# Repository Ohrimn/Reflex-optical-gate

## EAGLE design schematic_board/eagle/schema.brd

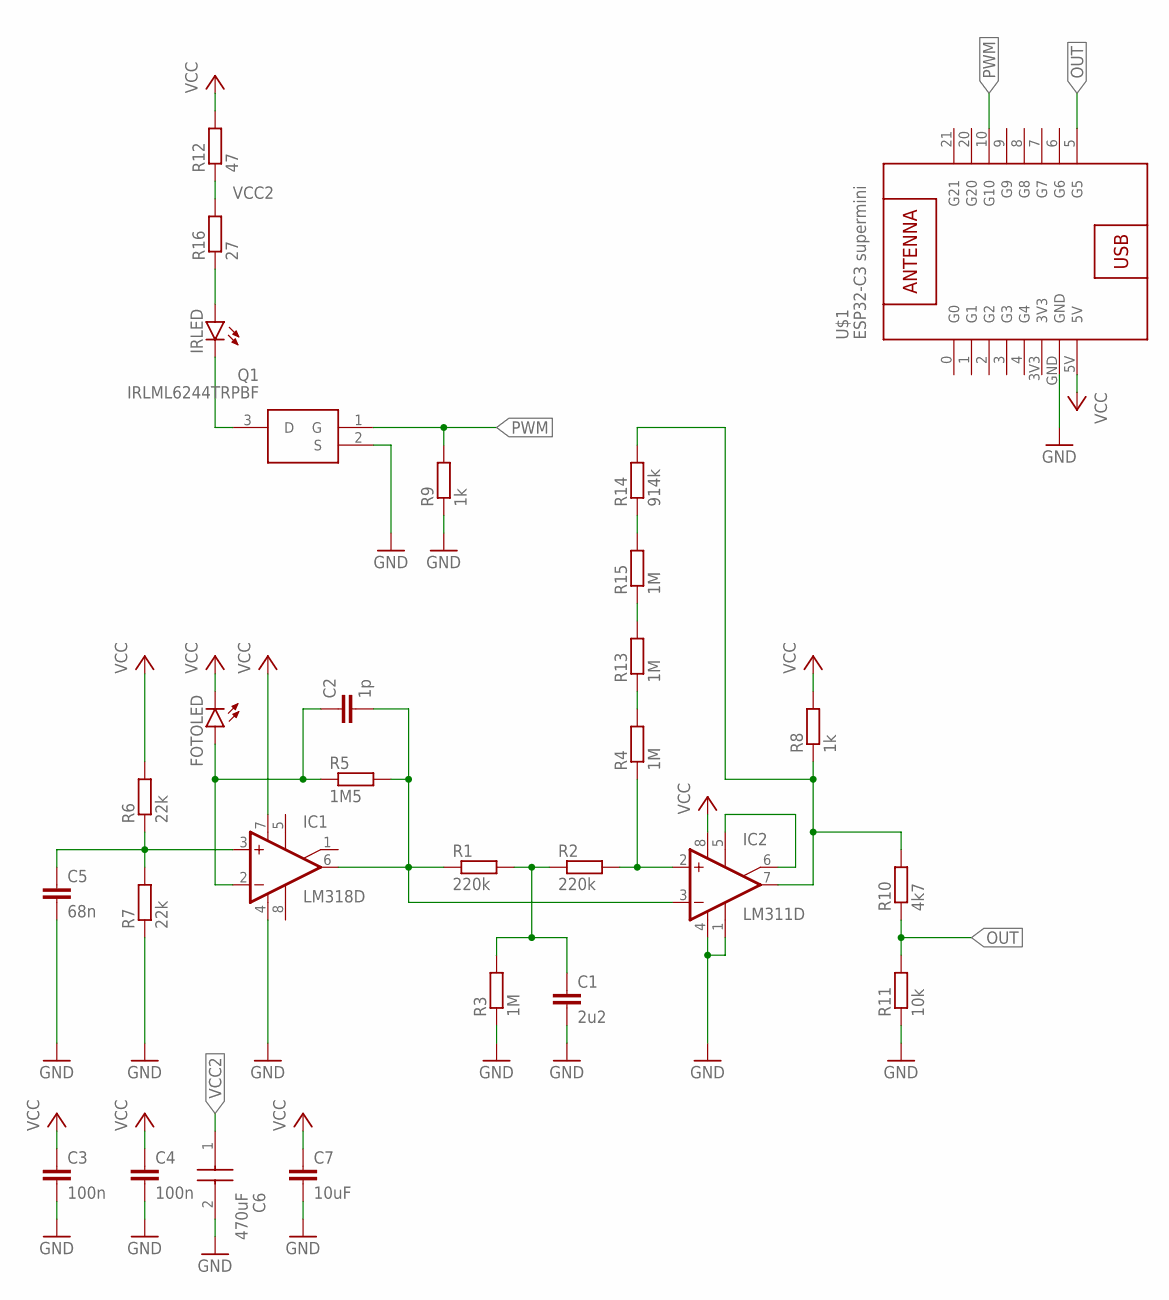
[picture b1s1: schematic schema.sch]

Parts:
C1: 2u2; C0603
C2: 1p; C0603K
C3, C4: 100n; C0603
C5: 68n; C0603
C6: 470uF; CAPAE830X1100N
C7: 10uF; C0603
FOTOLED: LED5MM
IC1: LM318D; SO08
IC2: LM311D; SO08
IRLED: LED5MM
Q1: IRLML6244TRPBF; SOT95P237X112-3N
R1, R2: 220k; R0603
R3, R4, R13, R15: 1M; R0603
R5: 1M5; R0603
R6, R7: 22k; R0603
R8, R9: 1k; R0603
R10: 4k7; R0603
R11: 10k; R0603
R12: 47; R0805
R14: 914k; R0603
R16: 27; R0805
U$1: ESP32-C3 supermini; ESP32-C3_SUPERMINI

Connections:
3V3: U$1.3V3
GND: C1.2, C3.2, C4.2, C5.2, C6.2 (-), C7.2, IC1.4 (V-), IC2.1 (GND), IC2.4 (V-), Q1.2 (S), R3.1, R7.1, R9.1, R11.1, U$1.GND
unnamed: C5.1, IC1.3 (+IN), R6.1, R7.2
unnamed: IC2.5 (ON), IC2.6 (ON/STR)
unnamed: IC2.2 (+IN), R2.2, R4.1
unnamed: C1.1, R1.2, R2.1, R3.2
unnamed: IRLED.K (C), Q1.3 (D)
unnamed: C2.2, IC1.6 (OUT), IC2.3 (-IN), R1.1, R5.2
unnamed: R4.2, R13.1
unnamed: IC2.7 (OUT), R8.1, R10.2, R14.2
unnamed: R13.2, R15.1
unnamed: R14.1, R15.2
unnamed: IRLED.A, R16.1
OUT: R10.1, R11.2, U$1.5 (G5)
PWM: Q1.1 (G), R9.2, U$1.10 (G10)
RE_C: C2.1, FOTOLED.A, IC1.2 (-IN), R5.1
VCC: C3.1, C4.1, C7.1, FOTOLED.K (C), IC1.7 (V+), IC2.8 (V+), R6.2, R8.2, R12.2, U$1.5V
VCC2: C6.1 (+), R12.1, R16.2

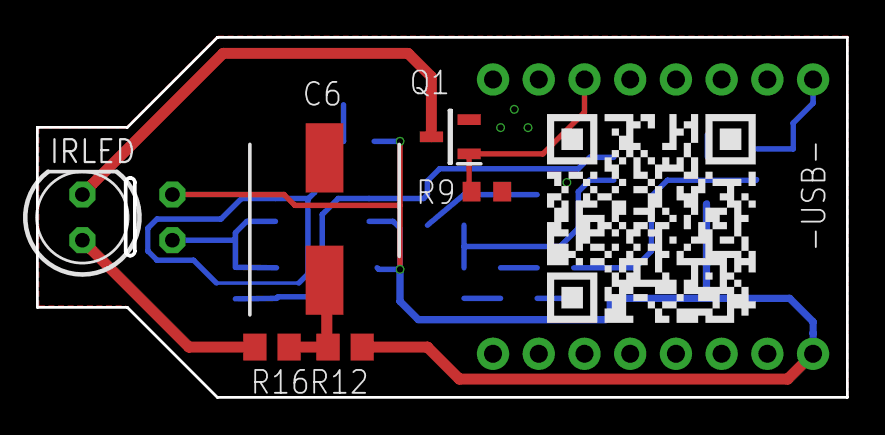
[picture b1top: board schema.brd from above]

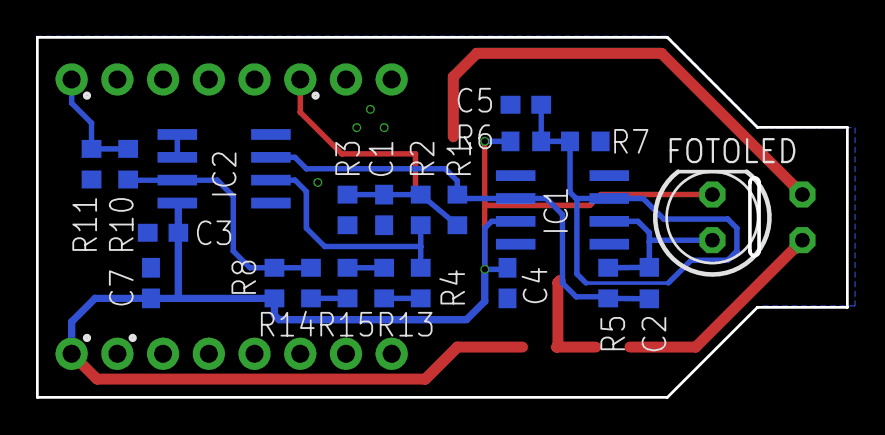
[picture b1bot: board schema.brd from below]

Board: 2 copper layers, 44.9 x 19.9 mm, 29 parts (22 on the bottom side), 17 nets.

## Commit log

2026-03-03 Initial release
2026-03-03 test
2026-03-03 Rename ahoj jsem tu.txt to ahoj.txt
2026-03-03 Latest code changes
2026-03-04 Latest schematic and board design
2026-03-04 Latest śchematic and board design
